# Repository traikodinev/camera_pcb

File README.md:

# Camera PCB

- `pcb.full` - full PCB including off-board components
- `pcb.reduced` - contains only the components that go on the board

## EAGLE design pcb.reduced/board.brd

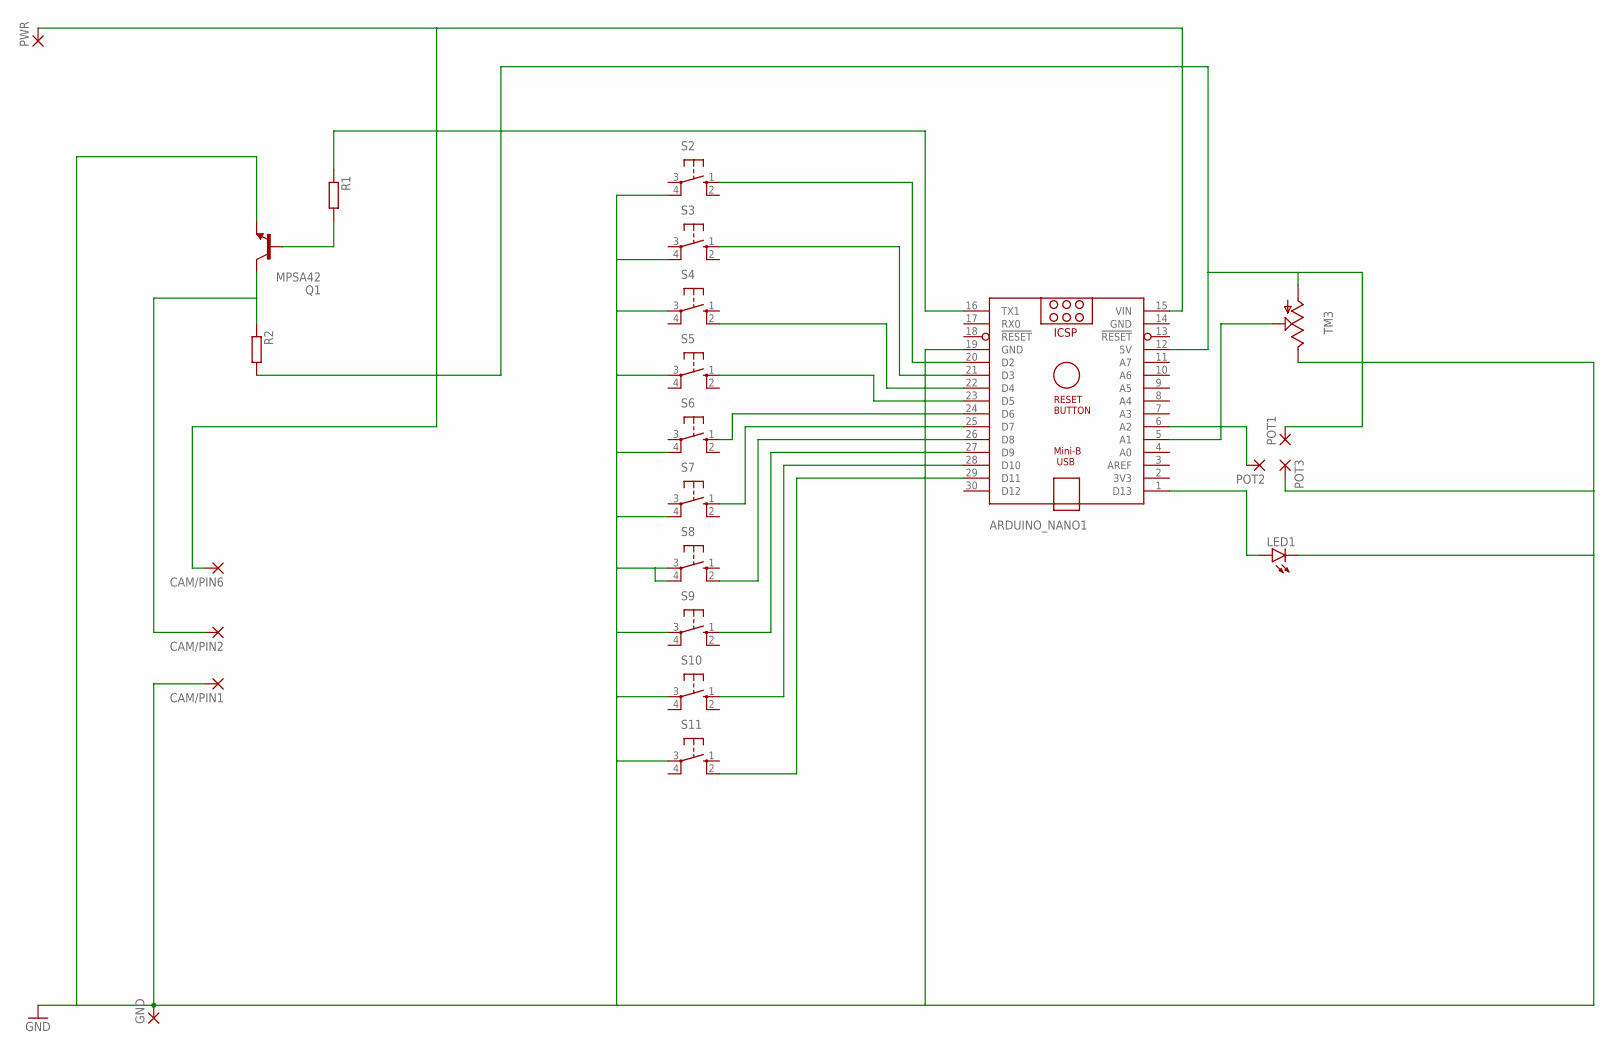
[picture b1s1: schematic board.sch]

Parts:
ARDUINO_NANO1: ARDUINO_NANO
CAM/PIN1, CAM/PIN2, CAM/PIN6: 1,6/0,8
GND: 1,6/0,8
LED1: LED5MM
POT1, POT2, POT3: 1,6/0,8
PWR: 1,6/0,8
Q1: MPSA42; TO92
R1, R2: R-EU_0204/2V; 0204V
S2, S3, S4, S5, S6, S7, S8, S9, S10, S11: 40-XX; B3F-40XX
TM3: TRIMSLIDE75; SLIDEPOT-75

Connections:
GND: ARDUINO_NANO1.14 (GND), ARDUINO_NANO1.19 (GND), CAM/PIN1.1, GND.1, LED1.K (C), POT3.1, Q1.3 (E), S2.4 (P1), S3.4 (P1), S4.3, S5.3, S6.4 (P1), S7.4 (P1), S8.3, S8.4 (P1), S9.3, S10.3, S11.3, TM3.B
unnamed: ARDUINO_NANO1.12 (5V), POT1.1, R2.2, TM3.A
unnamed: ARDUINO_NANO1.20 (D2), S2.1 (S)
unnamed: ARDUINO_NANO1.21 (D3), S3.1 (S)
unnamed: ARDUINO_NANO1.22 (D4), S4.2 (S1)
unnamed: ARDUINO_NANO1.23 (D5), S5.1 (S)
unnamed: ARDUINO_NANO1.24 (D6), S6.1 (S)
unnamed: ARDUINO_NANO1.25 (D7), S7.1 (S)
unnamed: ARDUINO_NANO1.26 (D8), S8.2 (S1)
unnamed: ARDUINO_NANO1.27 (D9), S9.1 (S)
unnamed: ARDUINO_NANO1.28 (D10), S10.1 (S)
unnamed: ARDUINO_NANO1.29 (D11), S11.2 (S1)
unnamed: ARDUINO_NANO1.15 (VIN), CAM/PIN6.1, PWR.1
unnamed: ARDUINO_NANO1.16 (TX1), R1.1
unnamed: Q1.2 (B), R1.2
unnamed: ARDUINO_NANO1.5 (A1), TM3.WIPER
unnamed: ARDUINO_NANO1.6 (A2), POT2.1
unnamed: CAM/PIN2.1, Q1.1 (C), R2.1
unnamed: ARDUINO_NANO1.1 (D13), LED1.A

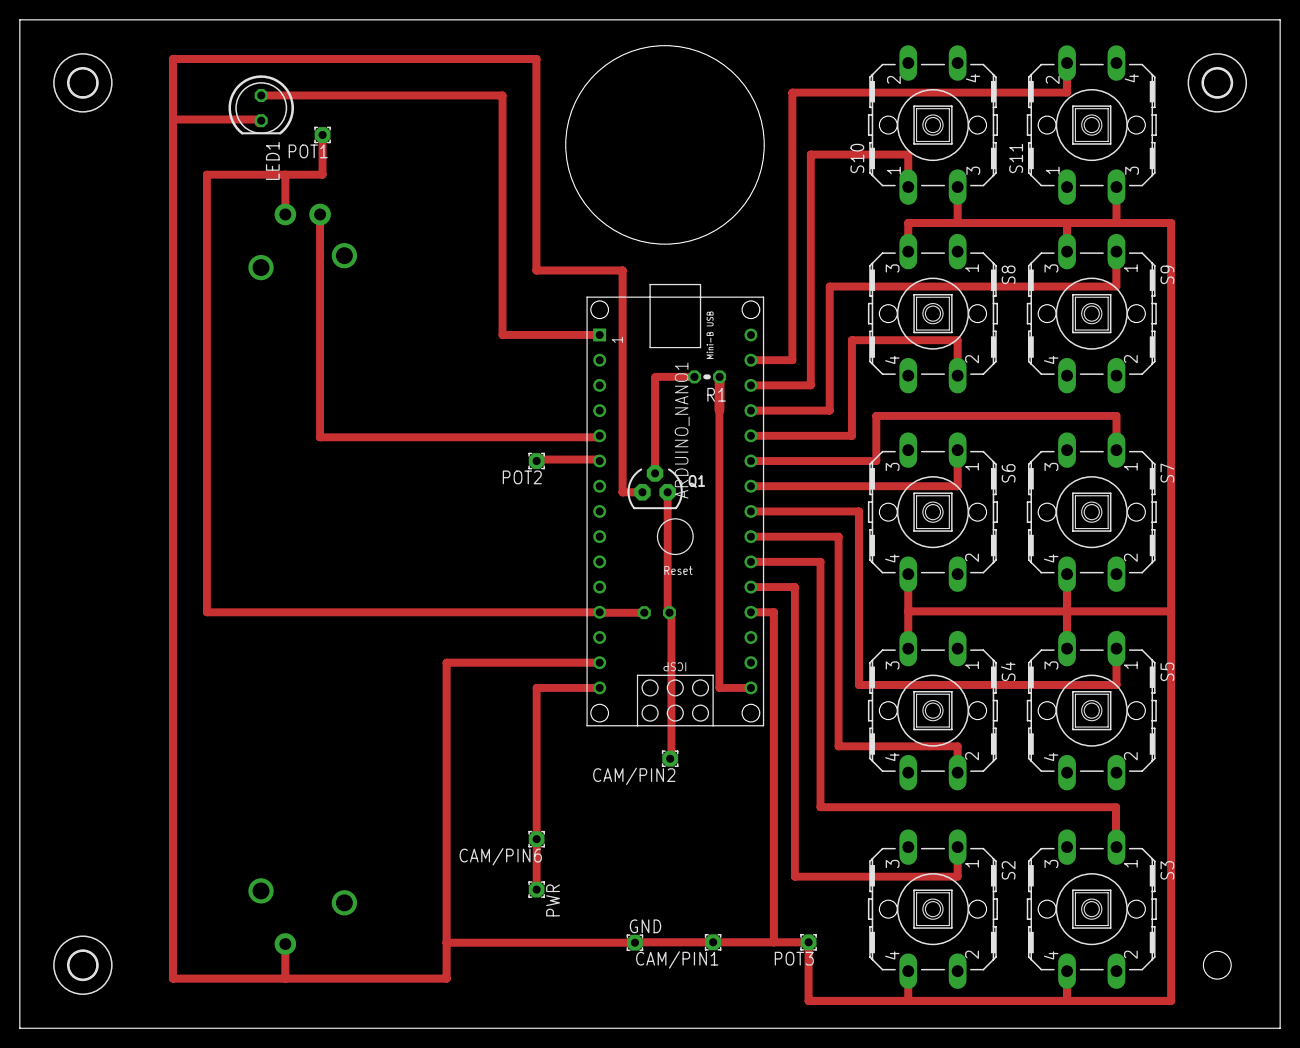
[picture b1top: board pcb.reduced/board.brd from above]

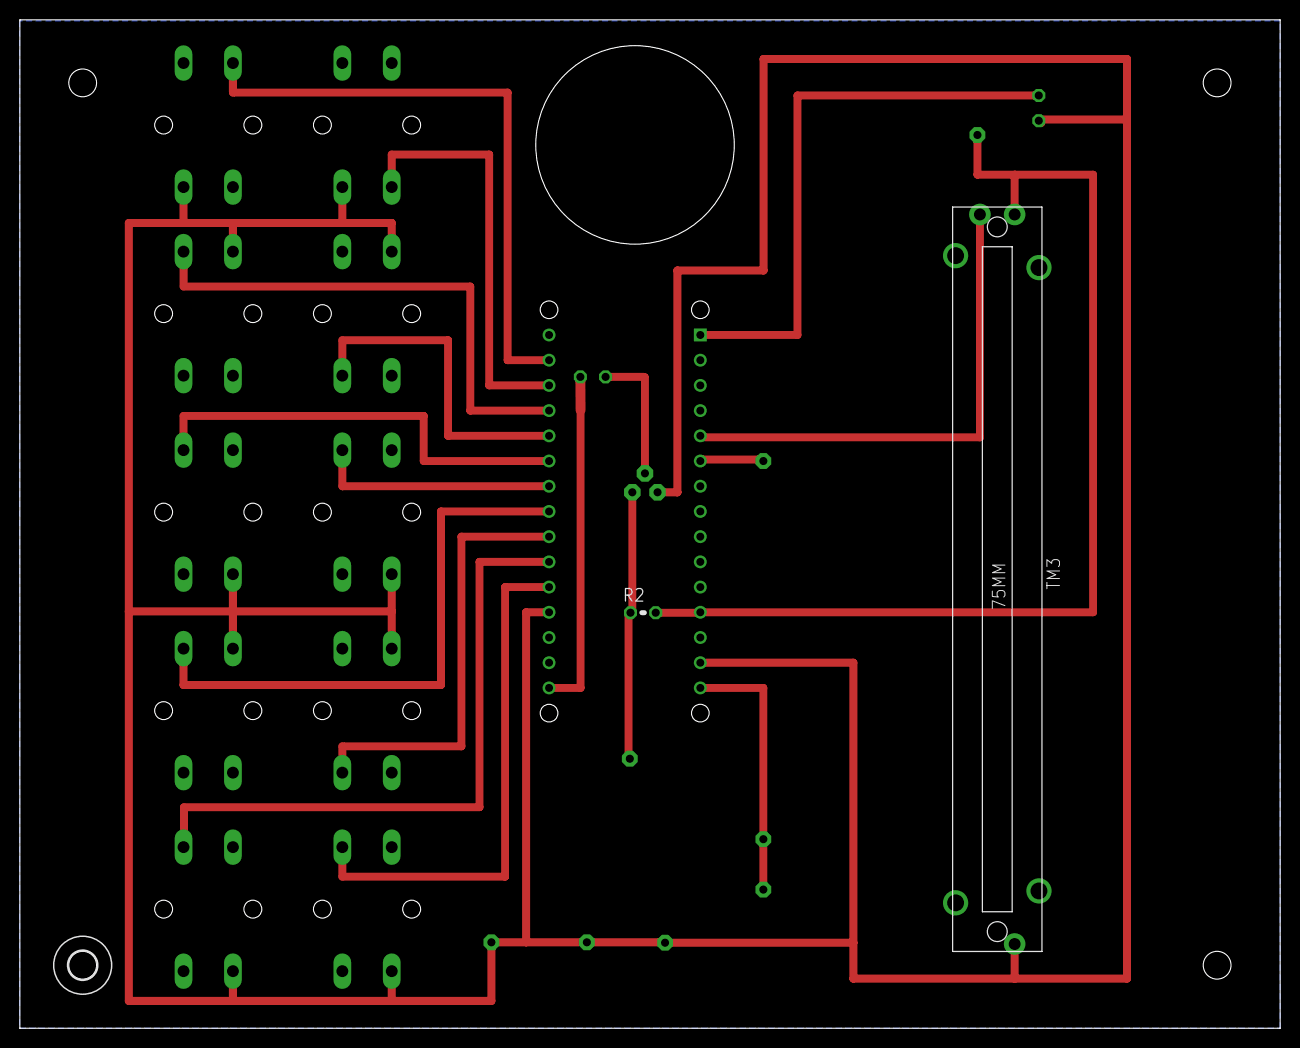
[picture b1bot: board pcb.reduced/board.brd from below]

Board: 2 copper layers, 127.0 x 101.6 mm, 28 parts (3 on the bottom side), 19 nets.

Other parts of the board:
U$1, U$2, U$3, U$4: 2,8

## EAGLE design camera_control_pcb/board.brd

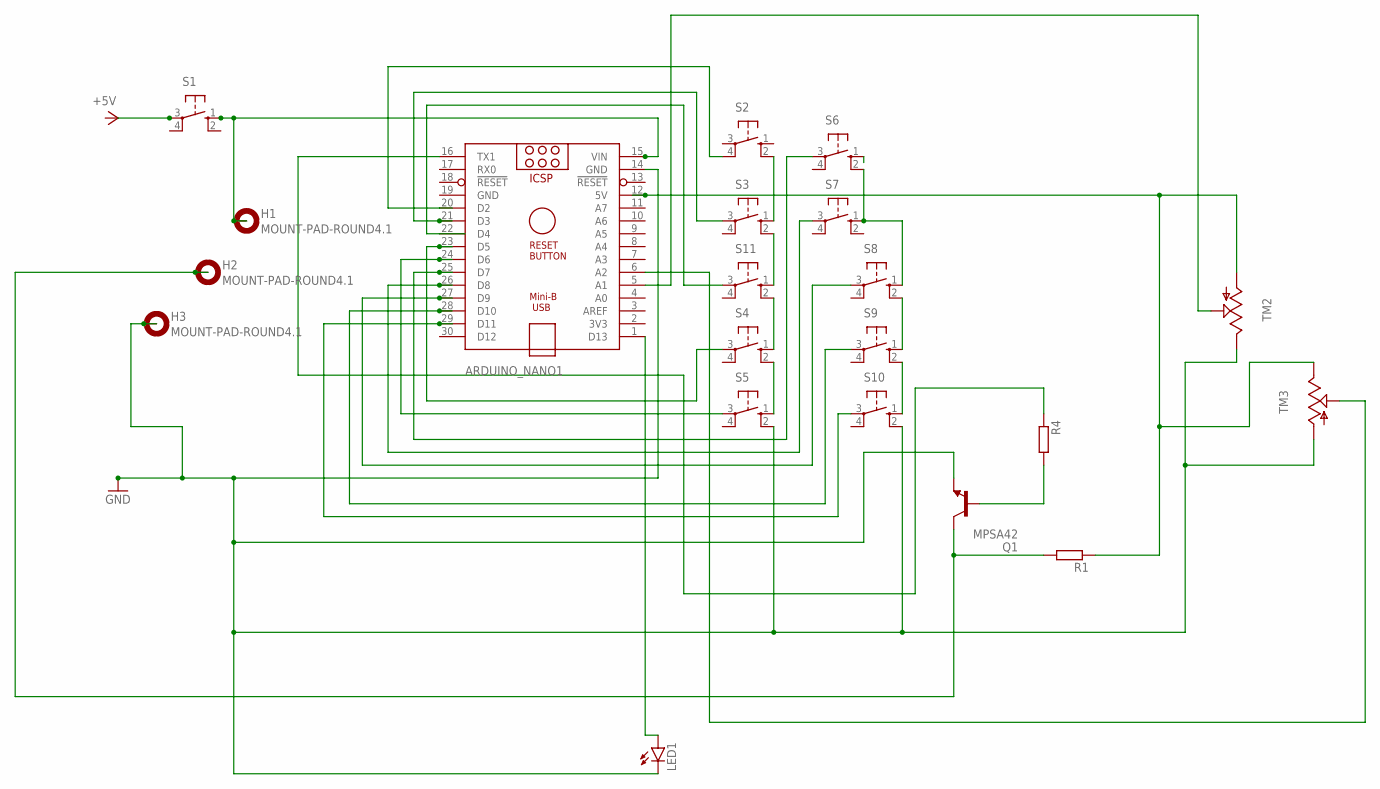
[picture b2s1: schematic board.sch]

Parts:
ARDUINO_NANO1: ARDUINO_NANO
H1, H2, H3: MOUNT-PAD-ROUND4.1; 4,1-PAD
LED1: LED5MM
Q1: MPSA42; TO92
R1, R4: R-EU_0204/2V; 0204V
S1: 40-XX; B3F-40XX
S2, S3, S4, S5, S6, S7, S8, S9, S10, S11: 10-XX; B3F-10XX
TM2, TM3: TRIMSLIDE75; SLIDEPOT-75

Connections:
unnamed: ARDUINO_NANO1.15 (VIN), H1.B4,1, S1.1 (S)
unnamed: ARDUINO_NANO1.14 (GND), ARDUINO_NANO1.19 (GND), H3.B4,1, LED1.K (C), Q1.3 (E), S5.2 (S1), S10.2 (S1), TM2.B, TM3.A
unnamed: Q1.2 (B), R4.2
unnamed: ARDUINO_NANO1.21 (D3), S3.3
unnamed: ARDUINO_NANO1.25 (D7), S6.3
unnamed: ARDUINO_NANO1.23 (D5), S4.3
unnamed: ARDUINO_NANO1.24 (D6), S5.3
unnamed: ARDUINO_NANO1.26 (D8), S7.3
unnamed: ARDUINO_NANO1.27 (D9), S8.3
unnamed: ARDUINO_NANO1.28 (D10), S9.3
unnamed: ARDUINO_NANO1.29 (D11), S10.3
unnamed: ARDUINO_NANO1.20 (D2), S2.4 (P1)
unnamed: ARDUINO_NANO1.22 (D4), S11.3
unnamed: ARDUINO_NANO1.16 (TX1), R4.1
unnamed: H2.B4,1, Q1.1 (C), R1.2
unnamed: ARDUINO_NANO1.12 (5V), R1.1, TM2.A, TM3.B
unnamed: ARDUINO_NANO1.5 (A1), TM2.WIPER
unnamed: ARDUINO_NANO1.6 (A2), TM3.WIPER
unnamed: S2.2 (S1), S3.1 (S)
unnamed: S3.2 (S1), S11.1 (S)
unnamed: S4.2 (S1), S5.1 (S)
unnamed: S6.2 (S1), S7.1 (S), S8.1 (S)
unnamed: S8.2 (S1), S9.1 (S)
unnamed: S9.2 (S1), S10.1 (S)
unnamed: S4.1 (S), S11.2 (S1)
unnamed: ARDUINO_NANO1.1 (D13), LED1.A

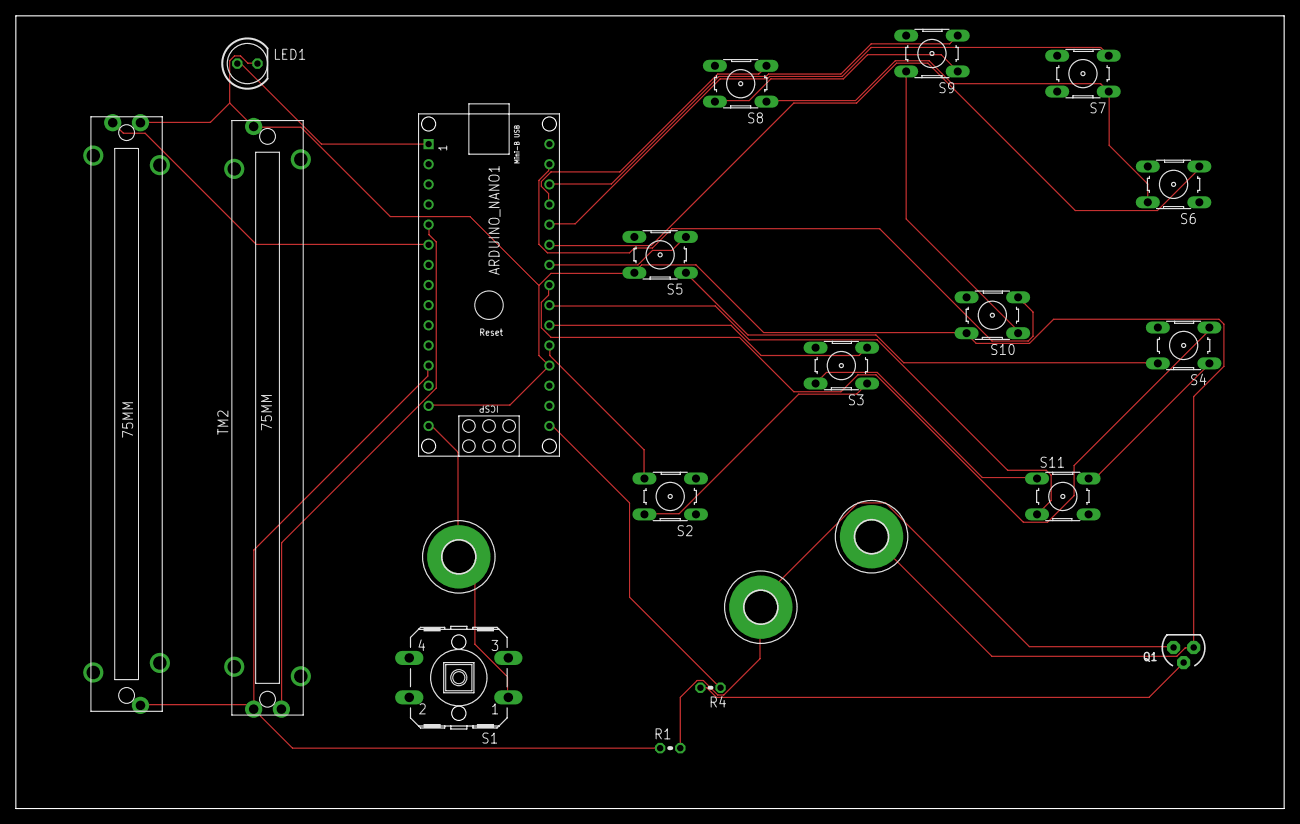
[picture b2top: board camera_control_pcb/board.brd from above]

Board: 2 copper layers, 160.0 x 100.0 mm, 21 parts (0 on the bottom side), 26 nets.

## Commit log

2019-06-12 init repo
2019-06-18 Add library and initial schematic.
2019-07-07 Rest of switch pins; demo board layout
2019-08-20 Finished placing components
2019-08-20 Fix switch sizes to 10mm
2019-08-20 Example Board Layout with 11 vias
2019-08-20 No vias board layout
2019-09-05 PCB Mark 2
2019-12-23 Clean-up repository
2019-12-23 Split board in two; clean up
2019-12-24 reduce grid size
2020-12-09 Add board pdfs
2020-12-11 Generate gerber files
2020-12-11 Gerber files zip
2020-12-11 update gerber files
2020-12-13 Final board layout
2020-12-13 Update cam job
2021-01-18 Use bigger buttons and re-layout.
